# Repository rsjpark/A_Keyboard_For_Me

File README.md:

# A_Keyboard_For_Me
CISC 4900 RPark

# Goals
A Keyboard For Me was designed to create a common tool from the ground up to customize the ergonomics and to be a learning experience

# Process
What we can design and have manufactured ourselves reasonably are the case, pcb, and plate. Other miscellaneous parts will be bought or are already in possession.

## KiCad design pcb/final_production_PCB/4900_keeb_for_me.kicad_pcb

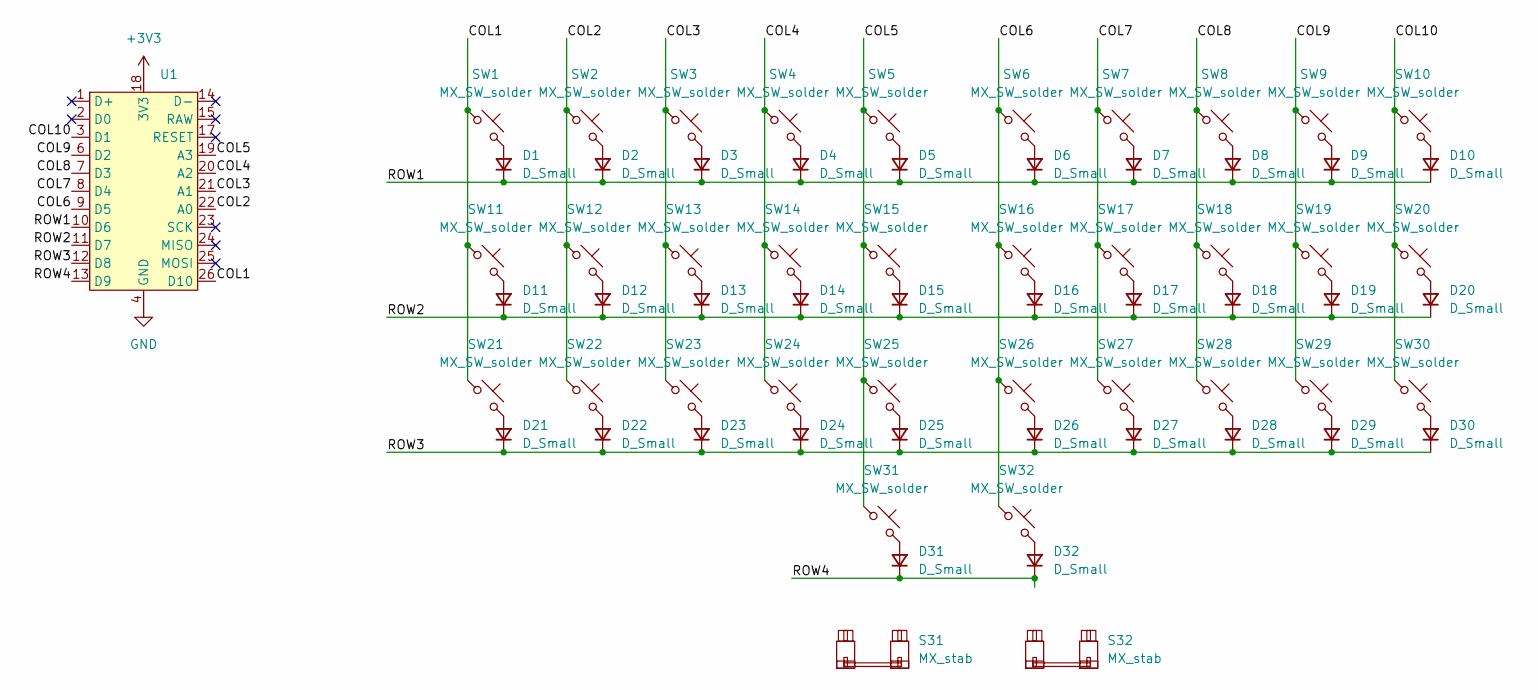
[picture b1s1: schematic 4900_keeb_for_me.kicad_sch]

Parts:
D1, D2, D3, D4, D5, D6, D7, D8, D9, D10, D11, D12, D13, D14, D15, D16, D17, D18, D19, D20, D21, D22, D23, D24, D25, D26, D27, D28, D29, D30, D31, D32: D_Small; D_DO-35_SOD27_P7.62mm_Horizontal
S31, S32: MX_stab; STAB_MX_P_2u
SW1, SW2, SW3, SW4, SW5, SW6, SW7, SW8, SW9, SW10, SW11, SW12, SW13, SW14, SW15, SW16, SW17, SW18, SW19, SW20, SW21, SW22, SW23, SW24, SW25, SW26, SW27, SW28, SW29, SW30, SW31, SW32: MX_SW_solder; SW_MX_1u
U1: Pro-Micro

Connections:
+3V3: U1.18 (3V3)
/COL1: SW1.1, SW11.1, SW21.1, U1.26 (D10)
/COL2: SW2.1, SW12.1, SW22.1, U1.22 (A0)
/COL3: SW3.1, SW13.1, SW23.1, U1.21 (A1)
/COL4: SW4.1, SW14.1, SW24.1, U1.20 (A2)
/COL5: SW5.1, SW15.1, SW25.1, SW31.1, U1.19 (A3)
/COL6: SW6.1, SW16.1, SW26.1, SW32.1, U1.9 (D5)
/COL7: SW7.1, SW17.1, SW27.1, U1.8 (D4)
/COL8: SW8.1, SW18.1, SW28.1, U1.7 (D3)
/COL9: SW9.1, SW19.1, SW29.1, U1.6 (D2)
/COL10: SW10.1, SW20.1, SW30.1, U1.3 (D1)
/ROW1: D1.1 (K), D2.1 (K), D3.1 (K), D4.1 (K), D5.1 (K), D6.1 (K), D7.1 (K), D8.1 (K), D9.1 (K), D10.1 (K), U1.10 (D6)
/ROW2: D11.1 (K), D12.1 (K), D13.1 (K), D14.1 (K), D15.1 (K), D16.1 (K), D17.1 (K), D18.1 (K), D19.1 (K), D20.1 (K), U1.11 (D7)
/ROW3: D21.1 (K), D22.1 (K), D23.1 (K), D24.1 (K), D25.1 (K), D26.1 (K), D27.1 (K), D28.1 (K), D29.1 (K), D30.1 (K), U1.12 (D8)
/ROW4: D31.1 (K), D32.1 (K), U1.13 (D9)
GND: U1.4 (GND), U1.5 (GND), U1.16 (GND)
unnamed: D1.2 (A), SW1.2
unnamed: D2.2 (A), SW2.2
unnamed: D3.2 (A), SW3.2
unnamed: D4.2 (A), SW4.2
unnamed: D5.2 (A), SW5.2
unnamed: D6.2 (A), SW6.2
unnamed: D7.2 (A), SW7.2
unnamed: D8.2 (A), SW8.2
unnamed: D9.2 (A), SW9.2
unnamed: D10.2 (A), SW10.2
unnamed: D11.2 (A), SW11.2
unnamed: D12.2 (A), SW12.2
unnamed: D13.2 (A), SW13.2
unnamed: D14.2 (A), SW14.2
unnamed: D15.2 (A), SW15.2
unnamed: D16.2 (A), SW16.2
unnamed: D17.2 (A), SW17.2
unnamed: D18.2 (A), SW18.2
unnamed: D19.2 (A), SW19.2
unnamed: D20.2 (A), SW20.2
unnamed: D21.2 (A), SW21.2
unnamed: D22.2 (A), SW22.2
unnamed: D23.2 (A), SW23.2
unnamed: D24.2 (A), SW24.2
unnamed: D25.2 (A), SW25.2
unnamed: D26.2 (A), SW26.2
unnamed: D27.2 (A), SW27.2
unnamed: D28.2 (A), SW28.2
unnamed: D29.2 (A), SW29.2
unnamed: D30.2 (A), SW30.2
unnamed: D31.2 (A), SW31.2
unnamed: D32.2 (A), SW32.2

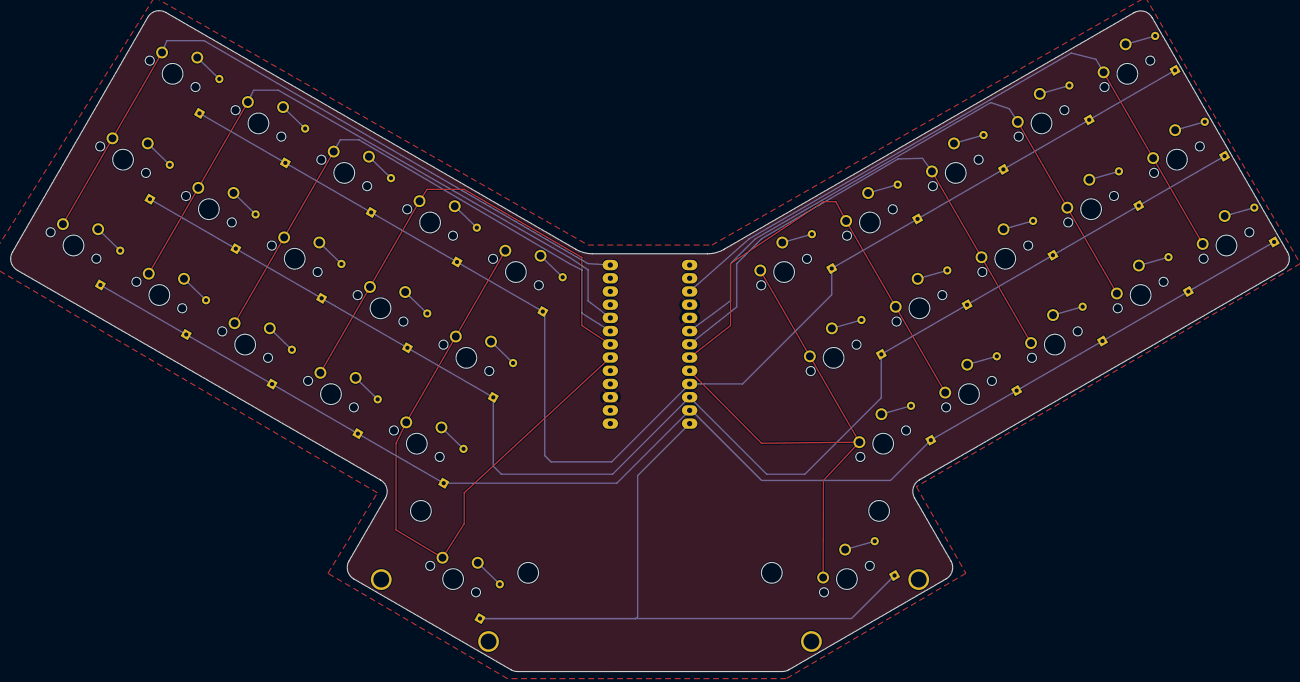
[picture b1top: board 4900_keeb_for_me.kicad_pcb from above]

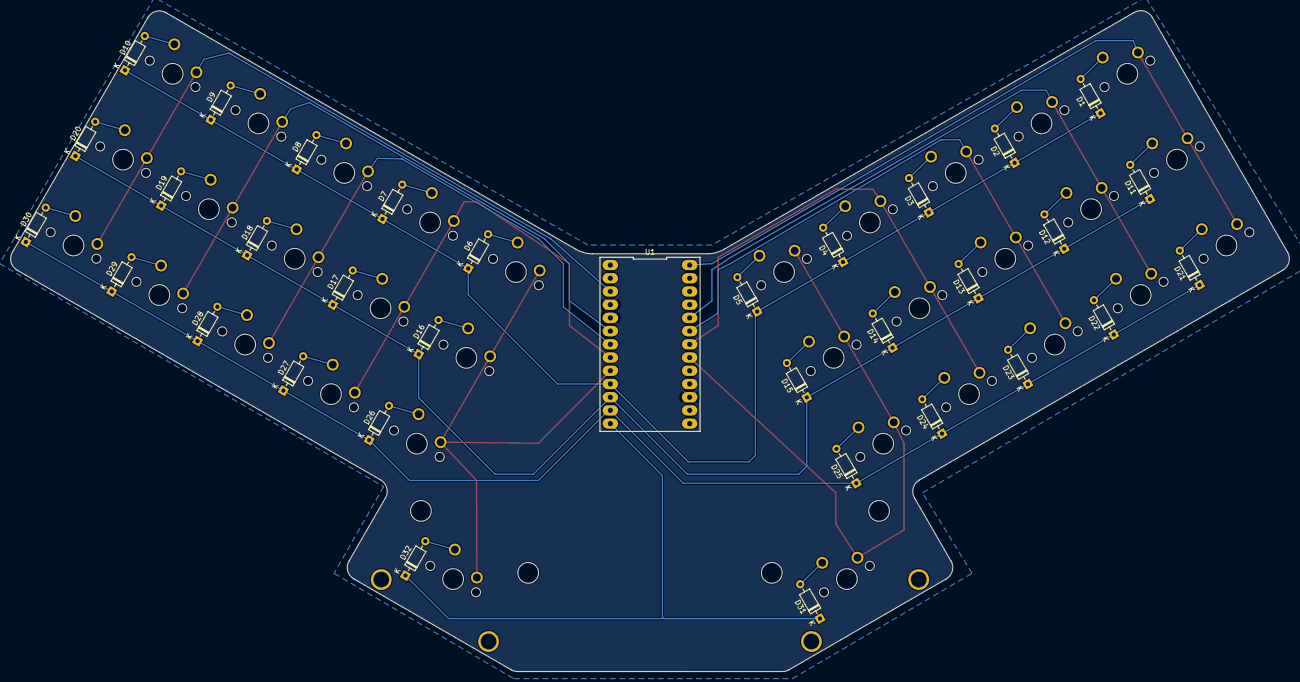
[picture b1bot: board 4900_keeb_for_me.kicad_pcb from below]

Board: 2 copper layers, 245.8 x 127.0 mm, 67 parts (33 on the bottom side), 47 nets.

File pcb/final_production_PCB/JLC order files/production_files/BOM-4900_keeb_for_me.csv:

Comment,Designator,Footprint,LCSC
MX_SW_solder,SW3,SW_MX_1u,
MX_SW_solder,SW21,SW_MX_1u,
MX_SW_solder,SW22,SW_MX_1u,
MX_SW_solder,SW17,SW_MX_1u,
MX_SW_solder,SW27,SW_MX_1u,
MX_SW_solder,SW15,SW_MX_1u,
MX_SW_solder,SW29,SW_MX_1u,
MX_SW_solder,SW1,SW_MX_1u,
MX_SW_solder,SW12,SW_MX_1u,
MX_SW_solder,SW13,SW_MX_1u,
MX_SW_solder,SW6,SW_MX_1u,
MX_SW_solder,SW28,SW_MX_1u,
MX_SW_solder,SW9,SW_MX_1u,
MX_SW_solder,SW19,SW_MX_1u,
MX_SW_solder,SW20,SW_MX_1u,
MX_stab,S32,STAB_MX_P_2u,
MX_SW_solder,SW31,SW_MX_1u,
MX_SW_solder,SW7,SW_MX_1u,
MX_SW_solder,SW4,SW_MX_1u,
MX_SW_solder,SW5,SW_MX_1u,
MX_SW_solder,SW18,SW_MX_1u,
MX_SW_solder,SW11,SW_MX_1u,
MX_SW_solder,SW2,SW_MX_1u,
MX_SW_solder,SW23,SW_MX_1u,
MX_SW_solder,SW14,SW_MX_1u,
MX_SW_solder,SW24,SW_MX_1u,
MX_stab,S31,STAB_MX_P_2u,
MX_SW_solder,SW25,SW_MX_1u,
MX_SW_solder,SW8,SW_MX_1u,
MX_SW_solder,SW16,SW_MX_1u,
MX_SW_solder,SW32,SW_MX_1u,
MX_SW_solder,SW10,SW_MX_1u,
MX_SW_solder,SW30,SW_MX_1u,
MX_SW_solder,SW26,SW_MX_1u,
D_Small,D21,D_DO-35_SOD27_P7.62mm_Horizontal,
D_Small,D16,D_DO-35_SOD27_P7.62mm_Horizontal,
D_Small,D7,D_DO-35_SOD27_P7.62mm_Horizontal,
D_Small,D11,D_DO-35_SOD27_P7.62mm_Horizontal,
D_Small,D15,D_DO-35_SOD27_P7.62mm_Horizontal,
D_Small,D18,D_DO-35_SOD27_P7.62mm_Horizontal,
D_Small,D17,D_DO-35_SOD27_P7.62mm_Horizontal,
D_Small,D28,D_DO-35_SOD27_P7.62mm_Horizontal,
D_Small,D2,D_DO-35_SOD27_P7.62mm_Horizontal,
D_Small,D1,D_DO-35_SOD27_P7.62mm_Horizontal,
D_Small,D25,D_DO-35_SOD27_P7.62mm_Horizontal,
D_Small,D19,D_DO-35_SOD27_P7.62mm_Horizontal,
D_Small,D24,D_DO-35_SOD27_P7.62mm_Horizontal,
D_Small,D31,D_DO-35_SOD27_P7.62mm_Horizontal,
D_Small,D22,D_DO-35_SOD27_P7.62mm_Horizontal,
D_Small,D30,D_DO-35_SOD27_P7.62mm_Horizontal,
D_Small,D29,D_DO-35_SOD27_P7.62mm_Horizontal,
D_Small,D3,D_DO-35_SOD27_P7.62mm_Horizontal,
~,U1,Pro-Micro,
D_Small,D5,D_DO-35_SOD27_P7.62mm_Horizontal,
D_Small,D27,D_DO-35_SOD27_P7.62mm_Horizontal,
D_Small,D13,D_DO-35_SOD27_P7.62mm_Horizontal,
D_Small,D23,D_DO-35_SOD27_P7.62mm_Horizontal,
D_Small,D26,D_DO-35_SOD27_P7.62mm_Horizontal,
D_Small,D20,D_DO-35_SOD27_P7.62mm_Horizontal,
D_Small,D14,D_DO-35_SOD27_P7.62mm_Horizontal,
D_Small,D8,D_DO-35_SOD27_P7.62mm_Horizontal,
D_Small,D6,D_DO-35_SOD27_P7.62mm_Horizontal,
D_Small,D10,D_DO-35_SOD27_P7.62mm_Horizontal,
D_Small,D4,D_DO-35_SOD27_P7.62mm_Horizontal,
D_Small,D32,D_DO-35_SOD27_P7.62mm_Horizontal,
D_Small,D9,D_DO-35_SOD27_P7.62mm_Horizontal,
D_Small,D12,D_DO-35_SOD27_P7.62mm_Horizontal,

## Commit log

2023-12-14 previous presentation and a list of resources used
2023-12-14 fusion exercise files, various .steps used for measuring, final case .step
2023-12-14 edits
2023-12-14 an example of the horrible routing, and the production pcb
2023-12-14 plate files
2023-12-14 all firmware related
2023-12-14 possible images to use in slide and presentation
2023-12-14 slide deck add
